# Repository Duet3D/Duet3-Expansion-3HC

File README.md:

# Duet3-Expansion-3HC
The Duet 3 Expansion 3HC board connects to the Duet 3 CAN-FD bus and provides 3 high current stepper driver channels, along with heaters, fans and GPIO. Multiple expansion boards can be daisy chained on the CAN-FD bus.

Product page is here: https://www.duet3d.com/Duet3Expansion3HC

Documentation is here: https://docs.duet3d.com/Duet3D_hardware/Duet_3_family/Duet_3_Mainboard_3HC_Hardware_Overview

As always please discuss this on the Duet3d forum: https://forum.duet3d.com/

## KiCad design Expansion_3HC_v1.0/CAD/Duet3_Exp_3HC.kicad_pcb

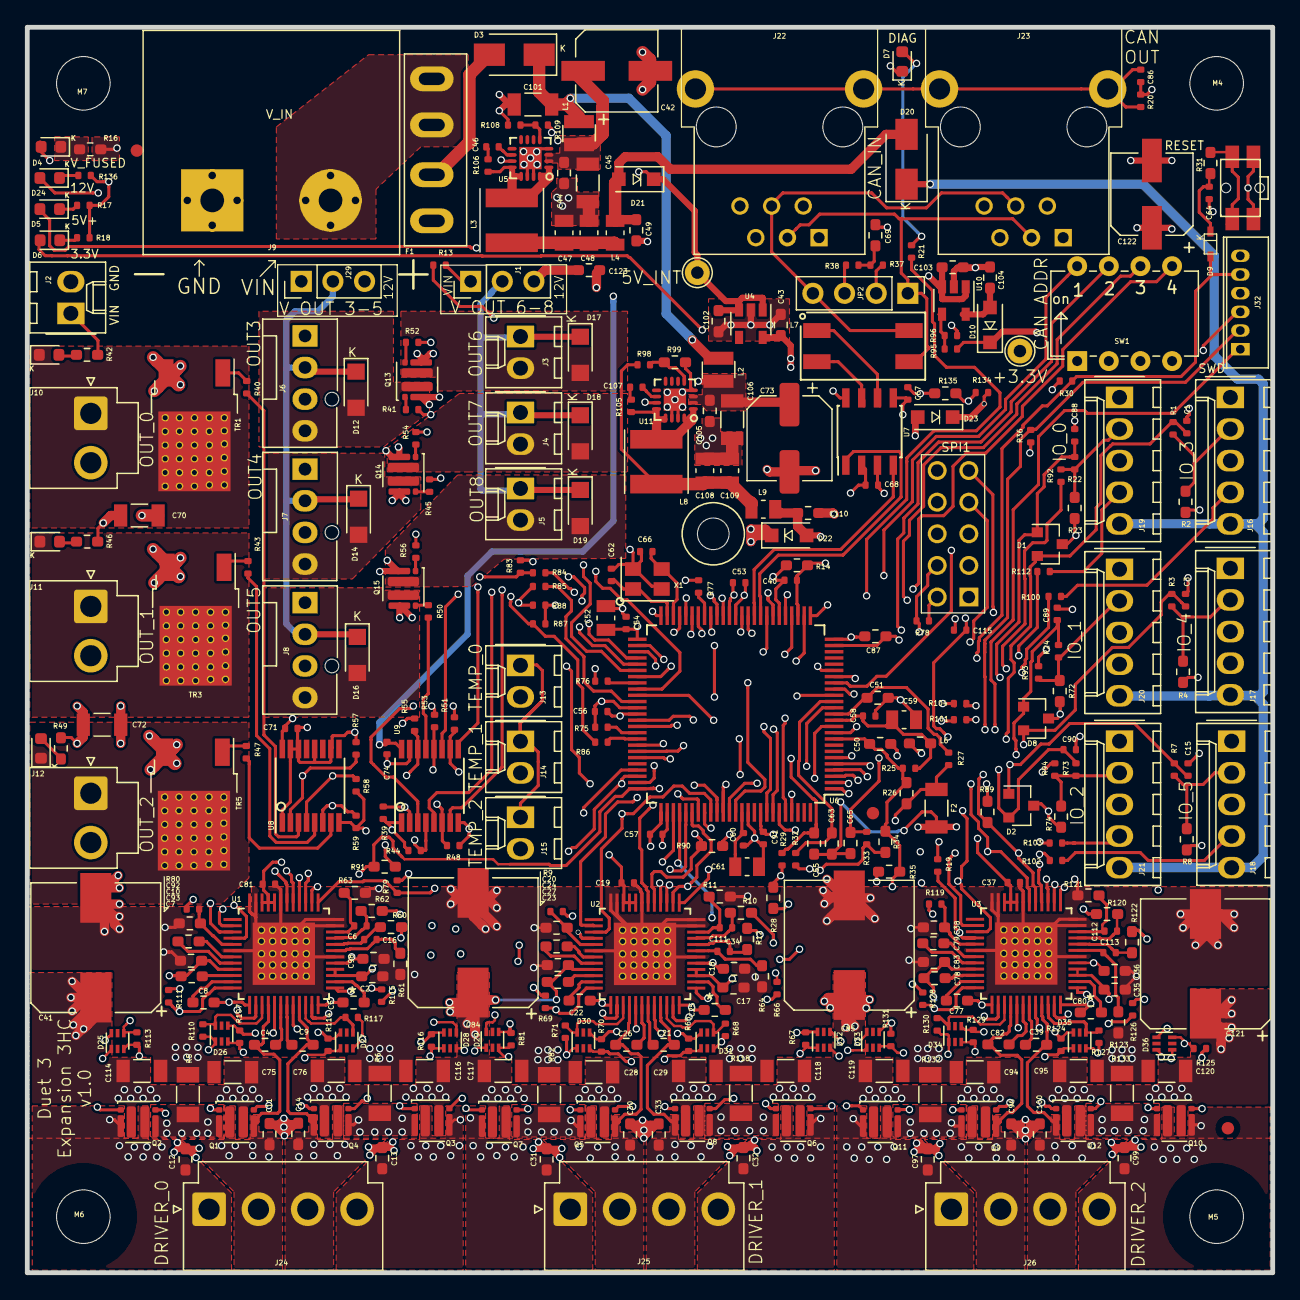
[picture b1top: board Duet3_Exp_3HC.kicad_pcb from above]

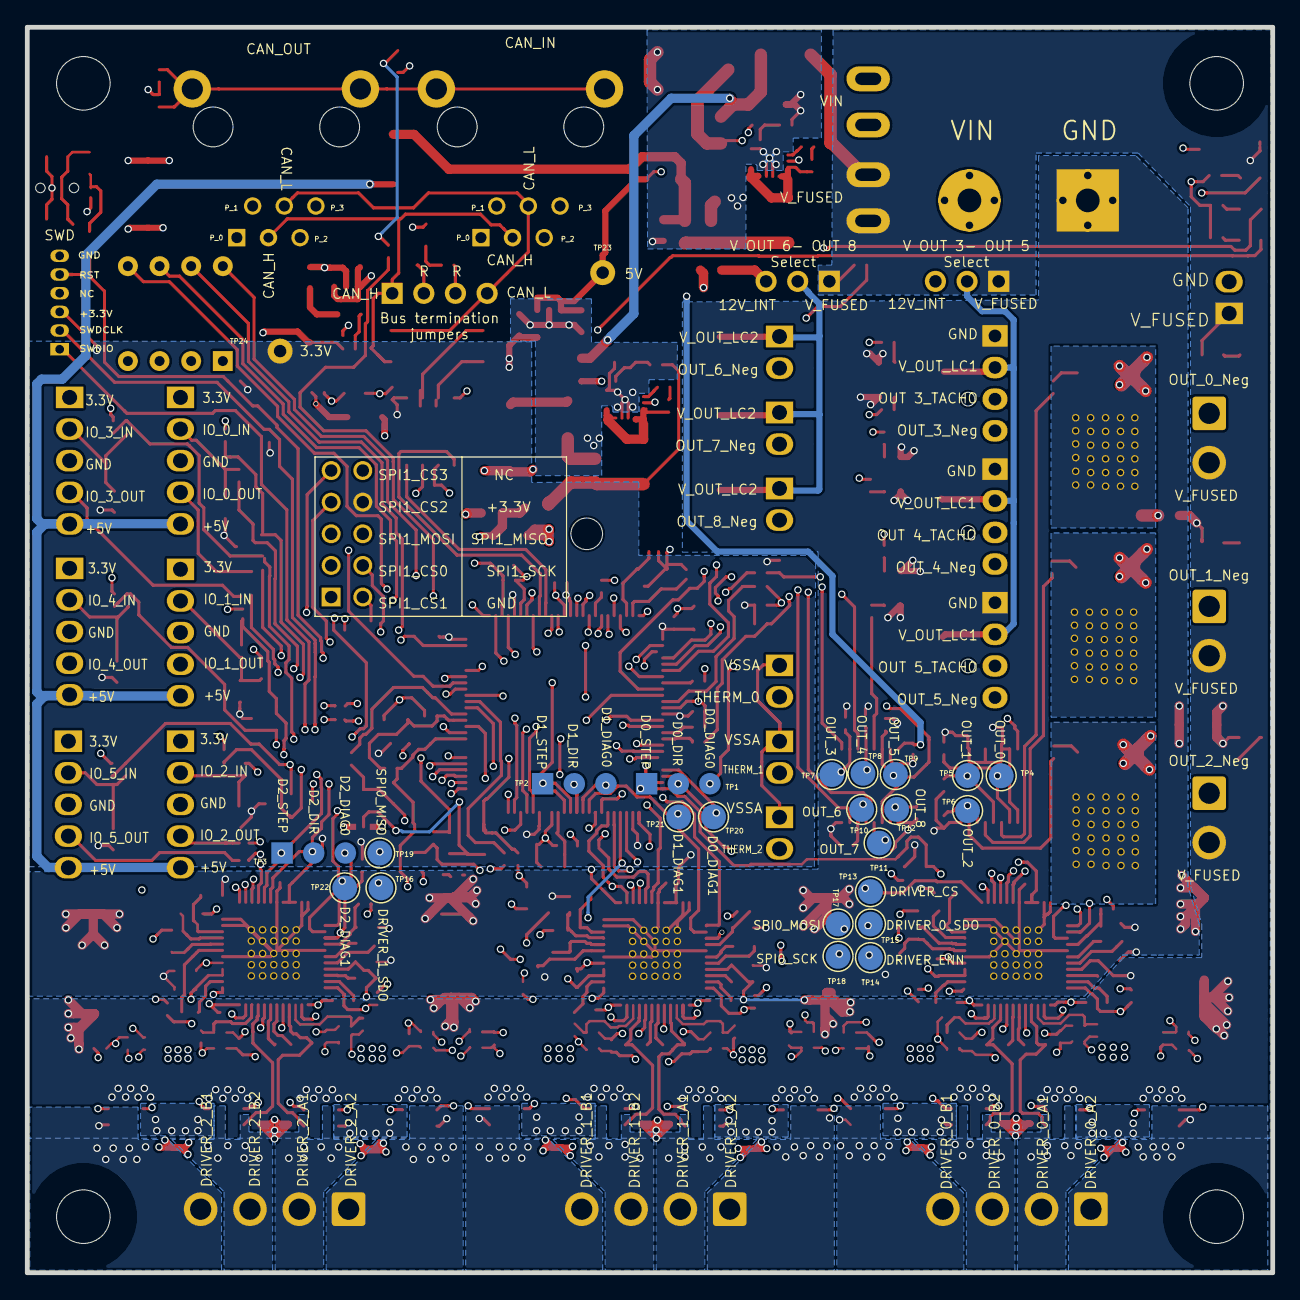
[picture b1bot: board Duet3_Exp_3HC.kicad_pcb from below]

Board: 4 copper layers, 100.0 x 100.0 mm, 398 parts (19 on the bottom side), 279 nets.

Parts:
C1, C3, C15, C88, C89, C90: 2n2 - DNP; C_0402_1005Metric_Wbry
C2, C17, C18, C35, C36, C50, C51, C55, C63, C65, C98: 2u2; C_0603_1608Metric_Wbry
C4, C5, C8, C9, C21, C22, C25, C26, C39, C77, C80, C82: 220n 16V; C_0603_1608Metric_Wbry
C6, C16, C34, C111, C112, C113: 2n2; C_0402_1005Metric_Wbry
C7, C23, C27, C44, C78, C83, C93, C105: 0u1 50V; C_0603_1608Metric_Wbry
C10, C24, C79: 22n X7R 10% 100V; C_0603_1608Metric_Wbry
C11, C12, C13, C14, C30, C31, C32, C33, C96, C97, C99, C100: 1n 100V; C_0603_1608Metric_Wbry
C19, C37, C46, C53, C54, C56, C57, C58, C60, C67, C68, C71, C74, C81, C91, C107: 0u1; C_0402_1005Metric_Wbry
C20, C38, C92: 470n 16V; C_0603_1608Metric_Wbry
C28, C29, C75, C76, C94, C95, C114, C116, C117, C118, C119, C120: 220n 100V; C_1206_3216Metric
C40, C64, C86, C115: 0u01; C_0402_1005Metric_Wbry
C41, C84, C85, C121: 220u 50V; CP_Elec_10x10
C42, C73: 100u 50V; CP_Elec_6.3x7.7
C43, C49, C102, C103, C104, C110, C123: 1u; C_0603_1608Metric_Wbry
C45, C70, C72, C101, C106: 10u 50V; C_1206_3216Metric
C47, C48, C108, C109: 22u; C_0805_2012Metric
C52, C59: 10u; C_0805_2012Metric
C61: 4u7; C_0805_2012Metric
C62, C66: 10p; C_0402_1005Metric_Wbry
C69: 4n7; C_0603_1608Metric_Wbry
C87: 1u 10V X75/X5R 10%; C_0603_1608Metric_Wbry
C122: 100u 16V+; CP_Elec_6.3x7.7
D1, D2, D8: BAT54C; SOT-23
D3: SK34ATR; D_SMA
D4: V_FUSED; LED_0603_1608Metric
D5: 5V+; LED_0603_1608Metric
D6: 3.3V; LED_0603_1608Metric
D7: DIAG; LED_0603_1608Metric
D9: 1N4448WT; SOD-523F
D10, D21, D22, D23: DSS14UTR; D_SOD-123F
D11: OUT_0; LED_0603_1608Metric
D12, D14, D16, D17, D18, D19: DO-219AB
D13: OUT_1; LED_0603_1608Metric
D15: OUT_2; LED_0603_1608Metric
D20: CDBA140-G; D_SMA
D24: 12V; LED_0603_1608Metric
D25, D26, D27, D28, D29, D30, D31, D32, D33, D34, D35, D36: BAT40V; SOT-563
F1: Mini Blade Fuse; MCCQ-122-minibladefuseholder
F2: VSSA FUSE; Fuse_1206_3216Metric
J1: V OUT 6-8; PinHeader_1x03_P2.54mm_Vertical
J2: VIN GND; Wurth_61900211121-1x02_P2.54mm_Vertical-(Molex_KK-254_AE-64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
J3: OUT6; Wurth_61900211121-1x02_P2.54mm_Vertical-(Molex_KK-254_AE-64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
J4: OUT7; Wurth_61900211121-1x02_P2.54mm_Vertical-(Molex_KK-254_AE-64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
J5: OUT8; Wurth_61900211121-1x02_P2.54mm_Vertical-(Molex_KK-254_AE-64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
J6: OUT3; FanPinHeader_1x04_P2.54mm_Vertical
J7: OUT4; FanPinHeader_1x04_P2.54mm_Vertical
J8: OUT5; FanPinHeader_1x04_P2.54mm_Vertical
J9: V_IN; screwt-barrier-9.5mm-1x2
J10: OUT0; JST_VH_B2P-VH-B_1x02_P3.96mm_Vertical
J11: OUT1; JST_VH_B2P-VH-B_1x02_P3.96mm_Vertical
J12: OUT2; JST_VH_B2P-VH-B_1x02_P3.96mm_Vertical
J13: TEMP_0; Wurth_61900211121-1x02_P2.54mm_Vertical-(Molex_KK-254_AE-64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
J14: TEMP_1; Wurth_61900211121-1x02_P2.54mm_Vertical-(Molex_KK-254_AE-64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
J15: TEMP_2; Wurth_61900211121-1x02_P2.54mm_Vertical-(Molex_KK-254_AE-64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
J16: IO_3; Wurth_61900511121-1x05_P2.54mm_Vertical(Molex_KK-254_AE-641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
J17: IO_4; Wurth_61900511121-1x05_P2.54mm_Vertical(Molex_KK-254_AE-641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
J18: IO_5; Wurth_61900511121-1x05_P2.54mm_Vertical(Molex_KK-254_AE-641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
J19: IO_0; Wurth_61900511121-1x05_P2.54mm_Vertical(Molex_KK-254_AE-641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
J20: IO_1; Wurth_61900511121-1x05_P2.54mm_Vertical(Molex_KK-254_AE-641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
J21: IO_2; Wurth_61900511121-1x05_P2.54mm_Vertical(Molex_KK-254_AE-641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
J22: CAN_IN; RJ11_6P6C_half_shield
J23: CAN_OUT; RJ11_6P6C_half_shield
J24: DRIVER_0; JST_VH_B4P-VH_1x04_P3.96mm_Vertical
J25: DRIVER_1; JST_VH_B4P-VH_1x04_P3.96mm_Vertical
J26: DRIVER_2; JST_VH_B4P-VH_1x04_P3.96mm_Vertical
J28: SPI1; MAX_TEMP_DB
J29: V OUT 3-5; PinHeader_1x03_P2.54mm_Vertical
J32: SWD; JST_ZH_1x06_P1.5_B6B-ZR-SM4-TF
JP2: Term_R; PinHeader_1x04_P2.54mm_Vertical
L1, L2: 1uH, 1A+; L_1008_2512Metric
L3, L8: 4u7; L_Taiyo-Yuden_NR-50xx
L4, L9: 100 ohm, 4 A; L_0805_2012Metric
L6: 1K @100Mhz; R_0603_1608Metric_Wbry
L7: CM Choke; DR331
M1, M2, M3: FID; Fiducial_1mm_Dia_2mm_Outer
M4, M5, M6, M7: MOUNTING; MountingHole_4.3mm_M4
NT1, NT2: Net-Tie_2; NetTie-2_SMD_Pad0.5mm
Q1, Q2, Q3, Q4, Q5, Q6, Q7, Q8, Q9, Q10, Q11, Q12, Q13, Q14, Q15: Q_DUAL_NMOS; Fairchild_DualPower33-6_3x3mm
R1, R3, R7, R19, R22, R24, R27, R29, R30, R32, R33, R39, R44, R48, R51, R53, R55, R57, R58, R59, R73, R78, R79, R83, R84, R85, R86, R87, R88, R92, R93, R94, R109: 10K; R_0402_1005Metric_Wbry
R2, R4, R8, R23, R72, R74: 27K; R_0603_1608Metric_Wbry
R5, R6, R82, R118, R132, R133: 0R05 1% 1W; R_1206_3216Metric_Pad1.24x1.80mm_HandSolder
R9, R80, R119: 2R2 1%; R_0402_1005Metric_Wbry
R10, R11, R12, R60, R61, R62, R63, R64, R120, R121, R122, R123: 47R 1%; R_0603_1608Metric_Wbry
R13, R98, R134: 60K4; R_0402_1005Metric_Wbry
R14, R16, R26, R42, R46, R49, R89, R90, R91, R99, R135: 4K7; R_0603_1608Metric_Wbry
R17, R108: 2K2; R_0402_1005Metric_Wbry
R18, R40, R43, R47: 180R; R_0402_1005Metric_Wbry
R20: 100K; R_0402_1005Metric_Wbry
R21, R36, R41, R45, R50, R52, R54, R56, R75: 1K; R_0402_1005Metric_Wbry
R25: 15R; R_0402_1005Metric_Wbry
R28, R34, R35: 2K2 0.1%; R_0603_1608Metric_Wbry
R31: 330R; R_0603_1608Metric_Wbry
R37, R38: 59R 1%; R_0402_1005Metric_Wbry
R65, R66, R67, R68, R69, R70, R71, R81, R107, R110, R111, R113, R114, R115, R116, R117, R124, R125, R126, R127, R128, R129, R130, R131: 150R; R_0402_1005Metric_Wbry
R76, R77: 1K - DNP; R_0402_1005Metric_Wbry
R95: 16K; R_0402_1005Metric_Wbry
R96: 5K1; R_0402_1005Metric_Wbry
R100, R101, R102, R103, R104, R112: 470R; R_0402_1005Metric_Wbry
R105, R106: 10R; R_0402_1005Metric_Wbry
R136: 4K7; R_0402_1005Metric_Wbry
S1: RESET; SW_SIDE_1_lugs
SW1: CAN ADDR; SW_DIP_SPSTx04_Slide_6.7x11.72mm_W7.62mm_P2.54mm_LowProfile
TP1: TP_D0; Test_Point_SMT_1x3
TP2: TP_D1; Test_Point_SMT_1x3
TP3: TP_D2; Test_Point_SMT_1x3
TP4: OUT_0; TestPoint_Pad_D2.0mm
TP5: OUT_1; TestPoint_Pad_D2.0mm
TP6: OUT_2; TestPoint_Pad_D2.0mm
TP7: OUT_3; TestPoint_Pad_D2.0mm
TP8: OUT_4; TestPoint_Pad_D2.0mm
TP9: OUT_5; TestPoint_Pad_D2.0mm
TP10: OUT_6; TestPoint_Pad_D2.0mm
TP11: OUT_7; TestPoint_Pad_D2.0mm
TP12: OUT_8; TestPoint_Pad_D2.0mm
TP13: DRIVER_CS; TestPoint_Pad_D2.0mm
TP14: DRIVER_ENN; TestPoint_Pad_D2.0mm
TP15: DRIVER_0_SDO; TestPoint_Pad_D2.0mm
TP16: DRIVER_1_SDO; TestPoint_Pad_D2.0mm
TP17: SPI0_MOSI; TestPoint_Pad_D2.0mm
TP18: SPI0_SCK; TestPoint_Pad_D2.0mm
TP19: SPI0_MISO; TestPoint_Pad_D2.0mm
TP20: D0_DIAG1; TestPoint_Pad_D2.0mm
TP21: D1_DIAG1; TestPoint_Pad_D2.0mm
TP22: D2_DIAG1; TestPoint_Pad_D2.0mm
TP23: 5V_INT; TestPoint_THTPad_D2.0mm_Drill1.0mm
TP24: +3.3V; TestPoint_THTPad_D2.0mm_Drill1.0mm
TR1, TR3, TR5: AOD4184A; TO-252-2_vias
U1, U2, U3: TMC5160; TMC5160-TA
U4: AP2127K-3.3; SOT-23-5
U5, U11: TS30041; QFN-16-1EP_3x3mm_P0.5mm_EP1.8x1.8mm
U6: SAME51N19; LQFP-100_14x14mm_P0.5mm
U7: MCP2542; SOIC-8_3.9x4.9mm_P1.27mm
U8, U9: 74HCT365; TSSOP-16_4.4x5mm_P0.65mm
U10: AP2127K-ADJ; SOT-23-5
X1: CRYSTAL_4PIN; Crystal_SMD_ECS-33B-4Pin_3.2x2.5mm

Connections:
3.3V_EXT: D10.1, J16.1, J17.1, J18.1, J19.1, J20.1, J21.1, R95.1
5V_EXT: D20.1, J16.5, J17.5, J18.5, J19.5, J20.5, J21.5
5V_INT: C68.1, C71.1, C74.1, C102.1, C103.1, D5.2, D21.1, R109.1, TP23.1, U4.1, U4.3, U7.3, U8.16, U9.16, U10.1, U10.3
12V_EXT: C123.1, D22.1, D24.2, J1.3, J29.3
12V_MON: C115.1, R134.2, R135.1, U6.10
12V_VG: C2.2, C17.2, C35.2, C122.1, D23.1, R134.1, U1.3, U1.4, U2.3, U2.4, U3.3, U3.4
+3.3V: C19.2, C37.2, C43.1, C52.1, C53.1, C54.1, C56.1, C57.1, C67.1, C81.2, C87.1, C91.1, D1.3, D2.3, D6.2, D8.3, J28.8, J32.3, L6.1, R2.2, R4.2, R8.2, R19.1, R23.2, R30.2, R36.1, R72.2, R74.2, R79.1, R83.2, R87.2, R88.2, TP24.1, U1.20, U1.21, U1.22, U2.20, U2.21, U2.22, U3.20, U3.21, U3.22, U4.5, U6.25, U6.30, U6.39, U6.51, U6.63, U6.77, U6.92, U7.5
/Headers/CAN_SHD_GND: C86.1, J22.7, J22.8, J23.7, J23.8, R20.1
/MOSFET outputs/out_0: R40.1, TR1.1
/MOSFET outputs/out_1: R43.1, TR3.1
/MOSFET outputs/out_2: R47.1, TR5.1
/MOSFET outputs/out_3: Q13.1, R41.1
/MOSFET outputs/out_4: Q14.4, R45.1
/MOSFET outputs/out_5: Q15.4, R50.1
/MOSFET outputs/out_6: Q13.4, R52.1
/MOSFET outputs/out_7: Q14.1, R54.1
/MOSFET outputs/out_8: Q15.1, R56.1
/Power/3.3_ADJ: R95.2, R96.1, U10.4
/Power/3.3_VOUT: C104.1, D10.2, U10.5
/Power/5V_BST: C46.2, U5.10
/Power/5V_COMMON: C49.1, D20.2, D21.2, L4.2
/Power/5V_FB: R108.1, R109.2, U5.5
/Power/5V_VCC: C42.1, C44.1, C45.1, L1.2, U5.2, U5.3, U5.11
/Power/5V_VSW: L3.2, R106.2, U5.1, U5.12, U5.13, U5.16
/Power/5_VOUT: C47.1, C48.1, L3.1, L4.1
/Power/12V_BST: C107.2, U11.10
/Power/12V_FB: R98.2, R99.1, U11.5
/Power/12V_VCC: C73.1, C105.1, C106.1, L2.2, U11.2, U11.3, U11.11
/Power/12V_VSW: L8.2, R105.2, U11.1, U11.12, U11.13, U11.16
/Power/12_VOUT: C108.1, C109.1, L8.1, L9.1, R98.1
/Power/L9_OUT: C110.1, D22.2, D23.2, L9.2
/Processor/CANH_C: L7.2, U7.7
/Processor/CANL_C: L7.1, U7.6
/Processor/IO_0_OUT_R: R112.2, U6.52
/Processor/IO_1_OUT_R: R104.2, U6.64
/Processor/IO_2_OUT_R: R103.2, U6.68
/Processor/IO_3_OUT_R: R100.1, U6.17
/Processor/IO_4_OUT_R: R101.2, U6.96
/Processor/IO_5_OUT_R: R102.2, U6.70
/Processor/RESET_SW: R31.1, S1.3, S1.4
/Processor/VDDCORE: C60.1, C61.1, U6.89
/Processor/XIN0: C66.1, U6.48, X1.3
/Processor/XOUT0: C62.1, U6.49, X1.1
/Processor/_RESET: C64.1, D9.1, R31.2
/Processor/out_3_tach: R84.1, U6.46
/Processor/out_4_tach: R86.2, U6.67
/Processor/out_5_tach: R85.2, U6.61
/Stepper Driver & Endstops/D0_5VOUT: C98.2, R80.1, U1.5
/Stepper Driver & Endstops/D0_CA1: C4.2, U1.42
/Stepper Driver & Endstops/D0_CA2: C8.2, U1.35
/Stepper Driver & Endstops/D0_CB1: C5.2, U1.2
/Stepper Driver & Endstops/D0_CB2: C9.2, U1.43
/Stepper Driver & Endstops/D0_CPI: C10.2, U1.31
/Stepper Driver & Endstops/D0_CPO: C10.1, U1.32
/Stepper Driver & Endstops/D0_HA1: D26.4, R107.1, U1.41
/Stepper Driver & Endstops/D0_HA2: D25.6, R111.1, U1.36
/Stepper Driver & Endstops/D0_HAG1: D26.3, Q1.4, R107.2
/Stepper Driver & Endstops/D0_HAG2: D25.1, Q2.1, R111.2
/Stepper Driver & Endstops/D0_HB1: D28.4, R115.1, U1.1
/Stepper Driver & Endstops/D0_HB2: D27.6, R114.1, U1.44
/Stepper Driver & Endstops/D0_HBG1: D28.3, Q3.4, R115.2
/Stepper Driver & Endstops/D0_HBG2: D27.1, Q4.1, R114.2
/Stepper Driver & Endstops/D0_LA1: D26.6, R110.1, U1.39
/Stepper Driver & Endstops/D0_LA2: D25.4, R113.1, U1.38
/Stepper Driver & Endstops/D0_LAG1: D26.1, Q1.1, R110.2
/Stepper Driver & Endstops/D0_LAG2: D25.3, Q2.4, R113.2
/Stepper Driver & Endstops/D0_LB1: D28.6, R116.1, U1.47
/Stepper Driver & Endstops/D0_LB2: D27.4, R117.1, U1.46
/Stepper Driver & Endstops/D0_LBG1: D28.1, Q3.1, R116.2
/Stepper Driver & Endstops/D0_LBG2: D27.3, Q4.4, R117.2
/Stepper Driver & Endstops/D0_SRAH: C16.2, R60.1, U1.8
/Stepper Driver & Endstops/D0_SRAL: C16.1, R61.1, U1.7
/Stepper Driver & Endstops/D0_SRAT: Q1.2, Q2.3, R5.2, R60.2
/Stepper Driver & Endstops/D0_SRBH: C6.2, R62.1, U1.9
/Stepper Driver & Endstops/D0_SRBL: C6.1, R63.1, U1.10
/Stepper Driver & Endstops/D0_SRBT: Q3.2, Q4.3, R6.2, R62.2
/Stepper Driver & Endstops/D0_VCC: C92.2, R80.2, U1.29
/Stepper Driver & Endstops/D0_VCP: C7.1, U1.34
/Stepper Driver & Endstops/D1_5VOUT: C18.2, R9.1, U2.5
/Stepper Driver & Endstops/D1_CA1: C26.2, U2.42
/Stepper Driver & Endstops/D1_CA2: C22.2, U2.35
/Stepper Driver & Endstops/D1_CB1: C25.2, U2.2
/Stepper Driver & Endstops/D1_CB2: C21.2, U2.43
/Stepper Driver & Endstops/D1_CPI: C24.2, U2.31
/Stepper Driver & Endstops/D1_CPO: C24.1, U2.32
/Stepper Driver & Endstops/D1_HA1: D30.4, R70.1, U2.41
/Stepper Driver & Endstops/D1_HA2: D29.6, R69.1, U2.36
/Stepper Driver & Endstops/D1_HAG1: D30.3, Q5.4, R70.2
/Stepper Driver & Endstops/D1_HAG2: D29.1, Q7.1, R69.2
/Stepper Driver & Endstops/D1_HB1: D32.4, R66.1, U2.1
/Stepper Driver & Endstops/D1_HB2: D31.6, R65.1, U2.44
/Stepper Driver & Endstops/D1_HBG1: D32.3, Q6.4, R66.2
/Stepper Driver & Endstops/D1_HBG2: D31.1, Q8.1, R65.2
/Stepper Driver & Endstops/D1_LA1: D30.6, R71.1, U2.39
/Stepper Driver & Endstops/D1_LA2: D29.4, R81.1, U2.38
/Stepper Driver & Endstops/D1_LAG1: D30.1, Q5.1, R71.2
/Stepper Driver & Endstops/D1_LAG2: D29.3, Q7.4, R81.2
/Stepper Driver & Endstops/D1_LB1: D32.6, R67.1, U2.47
/Stepper Driver & Endstops/D1_LB2: D31.4, R68.1, U2.46
/Stepper Driver & Endstops/D1_LBG1: D32.1, Q6.1, R67.2
/Stepper Driver & Endstops/D1_LBG2: D31.3, Q8.4, R68.2
/Stepper Driver & Endstops/D1_SRAH: C34.2, R12.1, U2.8
/Stepper Driver & Endstops/D1_SRAL: C34.1, R64.1, U2.7
/Stepper Driver & Endstops/D1_SRAT: Q5.2, Q7.3, R12.2, R82.2
/Stepper Driver & Endstops/D1_SRBH: C111.2, R10.1, U2.9
/Stepper Driver & Endstops/D1_SRBL: C111.1, R11.1, U2.10
/Stepper Driver & Endstops/D1_SRBT: Q6.2, Q8.3, R10.2, R118.2
/Stepper Driver & Endstops/D1_VCC: C20.2, R9.2, U2.29
/Stepper Driver & Endstops/D1_VCP: C23.1, U2.34
/Stepper Driver & Endstops/D2_5VOUT: C36.2, R119.1, U3.5
/Stepper Driver & Endstops/D2_CA1: C82.2, U3.42
/Stepper Driver & Endstops/D2_CA2: C77.2, U3.35
/Stepper Driver & Endstops/D2_CB1: C80.2, U3.2
/Stepper Driver & Endstops/D2_CB2: C39.2, U3.43
/Stepper Driver & Endstops/D2_CPI: C79.2, U3.31
/Stepper Driver & Endstops/D2_CPO: C79.1, U3.32
/Stepper Driver & Endstops/D2_HA1: D34.4, R129.1, U3.41
/Stepper Driver & Endstops/D2_HA2: D33.6, R128.1, U3.36
/Stepper Driver & Endstops/D2_HAG1: D34.3, Q9.4, R129.2
/Stepper Driver & Endstops/D2_HAG2: D33.1, Q11.1, R128.2
/Stepper Driver & Endstops/D2_HB1: D36.4, R125.1, U3.1
/Stepper Driver & Endstops/D2_HB2: D35.6, R124.1, U3.44
/Stepper Driver & Endstops/D2_HBG1: D36.3, Q10.4, R125.2
/Stepper Driver & Endstops/D2_HBG2: D35.1, Q12.1, R124.2
/Stepper Driver & Endstops/D2_LA1: D34.6, R130.1, U3.39
/Stepper Driver & Endstops/D2_LA2: D33.4, R131.1, U3.38
/Stepper Driver & Endstops/D2_LAG1: D34.1, Q9.1, R130.2
/Stepper Driver & Endstops/D2_LAG2: D33.3, Q11.4, R131.2
/Stepper Driver & Endstops/D2_LB1: D36.6, R126.1, U3.47
/Stepper Driver & Endstops/D2_LB2: D35.4, R127.1, U3.46
/Stepper Driver & Endstops/D2_LBG1: D36.1, Q10.1, R126.2
/Stepper Driver & Endstops/D2_LBG2: D35.3, Q12.4, R127.2
/Stepper Driver & Endstops/D2_SRAH: C113.2, R122.1, U3.8
/Stepper Driver & Endstops/D2_SRAL: C113.1, R123.1, U3.7
/Stepper Driver & Endstops/D2_SRAT: Q9.2, Q11.3, R122.2, R132.2
/Stepper Driver & Endstops/D2_SRBH: C112.2, R120.1, U3.9
/Stepper Driver & Endstops/D2_SRBL: C112.1, R121.1, U3.10
/Stepper Driver & Endstops/D2_SRBT: Q10.2, Q12.3, R120.2, R133.2
/Stepper Driver & Endstops/D2_VCC: C38.2, R119.2, U3.29
/Stepper Driver & Endstops/D2_VCP: C78.1, U3.34
BOARD_ID_0: SW1.8, U6.41
BOARD_ID_1: SW1.7, U6.42
BOARD_ID_2: SW1.6, U6.44
BOARD_ID_3: SW1.5, U6.45
BOARD_TYPE_0: R75.1, U6.66
BOARD_TYPE_1: R76.1, U6.58
BOARD_TYPE_2: R77.1, U6.43
CAN1RX: U6.35, U7.4
CAN1TX: U6.34, U7.1
CAN_H: J22.3, J23.3, JP2.1, L7.3
CAN_L: J22.4, J23.4, JP2.4, L7.4
DIAG_LED: R21.1, U6.40
DRIVER_0_A1: C4.1, C11.2, J24.2, Q1.3, Q1.5, U1.40
DRIVER_0_A2: C8.1, C12.2, J24.1, Q2.2, Q2.6, U1.37
DRIVER_0_B1: C5.1, C13.2, J24.4, Q3.3, Q3.5, U1.48
DRIVER_0_B2: C9.1, C14.2, J24.3, Q4.2, Q4.6, U1.45
DRIVER_0_DIAG0: TP1.3, U1.26, U6.27
DRIVER_0_DIAG1: TP20.1, U1.27, U6.72
DRIVER_0_DIR: TP1.2, U1.18, U6.73
DRIVER_0_SDO: TP15.1, U1.16, U2.15
DRIVER_0_STEP: R91.1, TP1.1, U1.17, U6.75
DRIVER_1_A1: C26.1, C30.2, J25.2, Q5.3, Q5.5, U2.40
DRIVER_1_A2: C22.1, C31.2, J25.1, Q7.2, Q7.6, U2.37
DRIVER_1_B1: C25.1, C32.2, J25.4, Q6.3, Q6.5, U2.48
DRIVER_1_B2: C21.1, C33.2, J25.3, Q8.2, Q8.6, U2.45
DRIVER_1_DIAG0: TP2.3, U2.26, U6.85
DRIVER_1_DIAG1: TP21.1, U2.27, U6.84
DRIVER_1_DIR: TP2.2, U2.18, U6.86
DRIVER_1_SDO: TP16.1, U2.16, U3.15
DRIVER_1_STEP: R90.1, TP2.1, U2.17, U6.87
DRIVER_2_A1: C82.1, C96.2, J26.2, Q9.3, Q9.5, U3.40
DRIVER_2_A2: C77.1, C97.2, J26.1, Q11.2, Q11.6, U3.37
DRIVER_2_B1: C80.1, C99.2, J26.4, Q10.3, Q10.5, U3.48
DRIVER_2_B2: C39.1, C100.2, J26.3, Q12.2, Q12.6, U3.45
DRIVER_2_DIAG0: TP3.3, U3.26, U6.95
DRIVER_2_DIAG1: TP22.1, U3.27, U6.97
DRIVER_2_DIR: TP3.2, U3.18, U6.1
DRIVER_2_STEP: R89.1, TP3.1, U3.17, U6.2
DRIVER_CS: R79.2, TP13.1, U1.13, U2.13, U3.13, U6.78
DRIVER_ENN: R19.2, TP14.1, U1.28, U2.28, U3.28, U6.79
GND: C1.2, C2.1, C3.2, C11.1, C12.1, C13.1, C14.1, C15.2, C17.1, C18.1, C19.1, C20.1, C27.2, C28.1, C29.1, C30.1, C31.1, C32.1, C33.1, C35.1, C36.1, C37.1, C38.1, C40.2, C41.2, C42.2, C43.2, C44.2, C45.2, C47.2, C48.2, C49.2, C50.2, C51.2, C52.2, C53.2, C54.2, C56.2, C57.2, C58.2, C59.2, C60.2, C61.2, C62.2, C64.2, C66.2, C67.2, C68.2, C69.1, C70.2, C71.2, C72.2, C73.2, C74.2, C75.1, C76.1, C81.1, C83.2, C84.2, C85.2, C86.2, C87.2, C88.2, C89.2, C90.2, C91.2, C92.1, C93.2, C94.1, C95.1, C96.1, C97.1, C98.1, C99.1, C100.1, C101.2, C102.2, C103.2, C104.2, C105.2, C106.2, C108.2, C109.2, C110.2, C114.1, C115.2, C116.1, C117.1, C118.1, C119.1, C120.1, C121.2, C122.2, C123.2, D7.1, J2.2, J6.1, J7.1, J8.1, J9.1, J16.3, J17.3, J18.3, J19.3, J20.3, J21.3, J28.2, J32.6, NT1.2, NT2.2, Q13.2, Q13.3, Q14.2, Q14.3, Q15.2, Q15.3, R5.1, R6.1, R11.2, R14.2, R16.2, R17.2, R18.2, R20.2, R39.1, R44.1, R48.1, R51.1, R53.1, R55.1, R57.1, R58.1, R59.1, R61.2, R63.2, R64.2, R75.2, R76.2, R77.2, R78.2, R82.1, R89.2, R90.2, R91.2, R96.2, R99.2, R108.2, R118.1, R121.2, R123.2, R132.1, R133.1, R135.2, R136.2, S1.1, S1.2, SW1.1, SW1.2, SW1.3, SW1.4, TR1.3, TR3.3, TR5.3, U1.6, U1.11, U1.12, U1.19, U1.23, U1.24, U1.30, U1.EPAD, U2.6, U2.11, U2.12, U2.19, U2.23, U2.24, U2.30, U2.EPAD, U3.6, U3.11, U3.12, U3.19, U3.23, U3.24, U3.30, U3.EPAD, U4.2, U5.4, U5.14, U5.15, U5.17, U6.24, U6.31, U6.38, U6.50, U6.62, U6.76, U6.90, U7.2, U7.8, U8.1, U8.8, U8.10, U8.12, U8.14, U8.15, U9.1, U9.8, U9.15, U10.2, U11.4, U11.14, U11.15, U11.17, X1.2, X1.4
GNDANA: C55.2, C63.2, C65.2, F2.2, NT1.1, NT2.1, U6.11
IO_0: C88.1, D1.1, R22.1, U6.19
IO_0_IN: J19.2, R22.2, R23.1, R92.2
IO_0_OUT: J19.4, R112.1
IO_1: C89.1, D8.1, R24.1, U6.5
IO_1_IN: J20.2, R24.2, R72.1, R93.2
IO_1_OUT: J20.4, R104.1
IO_2: C90.1, D2.2, R73.1, U6.3
IO_2_IN: J21.2, R73.2, R74.1, R94.2
IO_2_OUT: J21.4, R103.1
IO_3: C1.1, D1.2, R1.1, U6.60
IO_3_IN: J16.2, R1.2, R2.1
IO_3_OUT: J16.4, R100.2
IO_4: C3.1, D8.2, R3.1, U6.82
IO_4_IN: J17.2, R3.2, R4.1
IO_4_OUT: J17.4, R101.1
IO_5: C15.1, D2.1, R7.1, U6.4
IO_5_IN: J18.2, R7.2, R8.1
IO_5_OUT: J18.4, R102.1
unnamed: C46.1, R106.1
unnamed: C69.2, R37.2, R38.1
unnamed: C107.1, R105.1
unnamed: D4.1, R16.1
unnamed: D5.1, R17.1
unnamed: D6.1, R18.1
unnamed: D7.2, R21.2
unnamed: D11.2, R42.1
unnamed: D13.2, R46.1
unnamed: D15.2, R49.1
unnamed: D24.1, R136.1
unnamed: JP2.2, R37.1
unnamed: JP2.3, R38.2
OUT_0: R57.2, TP4.1, U6.54, U8.2
OUT_0_BUFF: R40.2, U8.3
OUT_0_NEG: D11.1, J10.1, TR1.2
OUT_1: R58.2, TP5.1, U6.55, U8.4
OUT_1_BUFF: R43.2, U8.5
OUT_1_NEG: D13.1, J11.1, TR3.2
OUT_2: R59.2, TP6.1, U6.74, U8.6
OUT_2_BUFF: R47.2, U8.7
OUT_2_NEG: D15.1, J12.1, TR5.2
OUT_3: R51.2, TP7.1, U6.16, U9.10
OUT_3_BUFF: R41.2, U9.9
OUT_3_NEG: D12.2, J6.4, Q13.5
OUT_3_TACHO: J6.3, R83.1, R84.2
OUT_4: R53.2, TP8.1, U6.18, U9.12
OUT_4_BUFF: R45.2, U9.11
OUT_4_NEG: D14.2, J7.4, Q14.6
OUT_4_TACHO: J7.3, R86.1, R87.1
OUT_5: R55.2, TP9.1, U6.26, U9.14
OUT_5_BUFF: R50.2, U9.13
OUT_5_NEG: D16.2, J8.4, Q15.6
OUT_5_TACHO: J8.3, R85.1, R88.1
OUT_6: R48.2, TP10.1, U6.29, U9.6
OUT_6_BUFF: R52.2, U9.7
OUT_6_NEG: D17.2, J3.2, Q13.6
OUT_7: R44.2, TP11.1, U6.33, U9.4
OUT_7_BUFF: R54.2, U9.5
OUT_7_NEG: D18.2, J4.2, Q14.5
OUT_8: R39.2, TP12.1, U6.47, U9.2
OUT_8_BUFF: R56.2, U9.3
OUT_8_NEG: D19.2, J5.2, Q15.5
P_0: J22.1, J23.1
P_1: J22.2, J23.2
P_2: J22.5, J23.5
P_3: J22.6, J23.6
RESET: D9.2, J32.5, R30.1, U6.88
SERIAL0_RXD: R92.1, U6.53
SERIAL1_RXD: R93.1, U6.65
SERIAL2_RXD: R94.1, U6.69
SPI0_MISO: TP19.1, U3.16, U6.83
SPI0_MOSI: TP17.1, U1.15, U6.80
SPI0_SCK: TP18.1, U1.14, U2.14, U3.14, U6.81
SPI1_CS0: J28.3, U6.32
SPI1_CS1: J28.1, U6.37
SPI1_CS2: J28.7, U6.20
SPI1_CS3: J28.9, U6.36
SPI1_MISO: J28.6, U6.59
SPI1_MOSI: J28.5, U6.56
SPI1_SCK: J28.4, R78.1, U6.57
SWDCLK: J32.2, R36.2, U6.93
SWDIO: J32.1, U6.94
TEMP_0: C55.1, R29.2, U6.6
TEMP_1: C63.1, R32.2, U6.15
TEMP_2: C65.1, R33.2, U6.14
THERMISTOR_0: J13.2, R28.2, R29.1
THERMISTOR_1: J14.2, R32.1, R35.2
THERMISTOR_2: J15.2, R33.1, R34.2
VDDANA: C58.1, C59.1, L6.2, R25.1, U6.12
VIN_POWER_MON: C40.1, R13.2, R14.1, U6.28
VREF_MON: C50.1, R25.2, R26.1, R28.1, R34.1, R35.1, U6.9
VSSA: F2.1, J13.1, J14.1, J15.1, R26.2, R27.1
VSSA_MON: C51.1, R27.2, U6.13
V_BK_IN: C101.1, D3.1, L1.1, L2.1
V_FUSED: C7.2, C23.2, C27.1, C28.2, C29.2, C41.1, C70.1, C72.1, C75.2, C76.2, C78.2, C83.1, C84.1, C85.1, C93.1, C94.2, C95.2, C114.2, C116.2, C117.2, C118.2, C119.2, C120.2, C121.1, D3.2, D4.2, F1.1, J1.1, J2.1, J10.2, J11.2, J12.2, J29.1, Q1.6, Q2.5, Q3.6, Q4.5, Q5.6, Q6.6, Q7.5, Q8.5, Q9.6, Q10.6, Q11.5, Q12.5, R13.1, R42.2, R46.2, R49.2, U1.33, U2.33, U3.33
V_IN: F1.2, J9.2
V_OUTLC1: D12.1, D14.1, D16.1, J6.2, J7.2, J8.2, J29.2
V_OUTLC2: D17.1, D18.1, D19.1, J1.2, J3.1, J4.1, J5.1

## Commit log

2020-02-28 Added description, links and image
2020-02-28 Added Schematic and Step file
2020-06-17 Added wiring & dimension svgs
2020-09-11 Fixed typos in wiring diagram
2020-11-19 Added Duet 3 License
2020-11-23 Rename License file
2020-11-23 Update Duet3_Exp_3HC_Schematic_v1.0.pdf
    Prep for Release
2020-11-23 Added iBOM
2020-11-23 Added KiCAD project
2023-09-28 1.02

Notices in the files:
Expansion_3HC_v1.0/CAD/Duet3_Exp_3HC.kicad_pcb:
See License here https://github.com/Duet3D/Duet3-Expansion-3HC/blob/master/LICENSE
